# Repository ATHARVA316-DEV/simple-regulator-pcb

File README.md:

# SIMPLE REGULATOR PCB 🔌

## Project Overview
SIMPLE REGULATOR is a compact 2-layer linear voltage regulator PCB designed for beginner and academic use.  
This project demonstrates basic voltage regulation, PCB layout practices, and component placement using minimal components.

---

## Key Features
- Simple linear voltage regulator design  
- 2-layer PCB  
- Compact and minimal footprint  
- Input and output status LEDs  
- Beginner-friendly educational project  

---

## Components Used
| Reference | Component |
|---------|----------|
| U1 | Linear Voltage Regulator IC |
| R1, R2 | Resistors |
| C1, C2, C3 | Decoupling and filter capacitors |
| D1, D2 | LED indicators |
| J1 | Input connector |
| J2 | Output connector |

---

## Working Principle
1. DC input is supplied through connector J1  
2. Input LED (D1) indicates power availability  
3. The regulator IC (U1) stabilizes the input voltage  
4. Capacitors filter noise and improve voltage stability  
5. Regulated output is available at connector J2  
6. Output LED (D2) confirms regulated voltage  

---

## PCB Specifications
- Board Size: 46.45 mm × 15.44 mm  
- Layers: 2  
- Drill Size: 1.0 mm (4 holes)  
- Copper Pour: Ground plane  
- Design Tool: KiCad  

---

## Project Images
## Custom Etched PCB

Below is the manually fabricated PCB for the Simple Regulator project.  
The board was created using the **chemical etching method on an FR4 copper board**.

### Circuit Schematic

### PCB Routing

### 3D PCB View

### PCB Layout

### Drill Map

---

## How to Use
1. Provide DC input voltage at J1  
2. Ensure input voltage is within regulator specifications  
3. Check input LED for power indication  
4. Use regulated output from J2  

---

## Learning Outcomes
- Understanding linear voltage regulation  
- Basic PCB routing techniques  
- Decoupling capacitor placement  
- Ground plane implementation  

---

## License
This project is licensed under the MIT License.

---

## Author
Designed by Atharva M  
---

## Acknowledgment
This project was developed for academic and learning purposes.

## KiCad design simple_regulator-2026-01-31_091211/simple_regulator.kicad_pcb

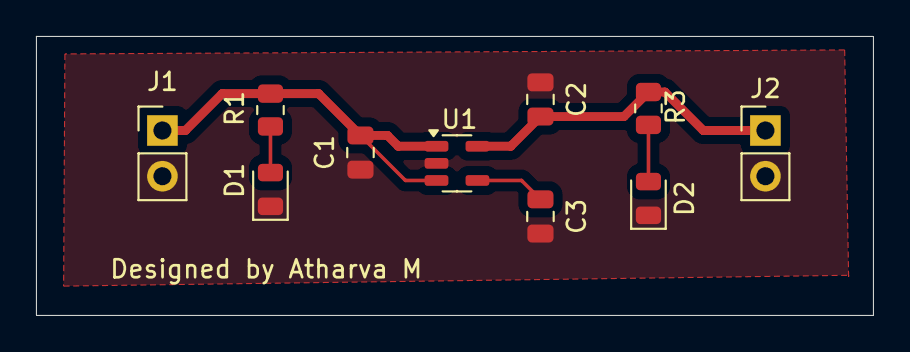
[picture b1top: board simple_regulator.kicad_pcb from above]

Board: 2 copper layers, 46.5 x 15.5 mm, 10 parts (0 on the bottom side), 6 nets.

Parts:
C1: 0.1uF; C_0805_2012Metric
C2: 2.2uF; C_0805_2012Metric
C3: 0.01uF; C_0805_2012Metric
D1: LED-RED; LED_0805_2012Metric
D2: LED-GREEN; LED_0805_2012Metric
J1, J2: Conn_01x02; PinHeader_1x02_P2.54mm_Vertical
R1: 649; R_0805_2012Metric
R3: 280; R_0805_2012Metric
U1: TPS79333-EP; SOT-23-5

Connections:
GND: C1.2, C2.2, C3.2, D1.1 (K), D2.1 (K), J1.2, J2.2, U1.2 (GND)
unnamed: D1.2 (A), R1.2
unnamed: D2.2 (A), R3.2
unnamed: C1.1, J1.1, R1.1, U1.1 (IN), U1.3 (EN)
unnamed: C2.1, J2.1, R3.1, U1.5 (OUT)
unnamed: C3.1, U1.4 (BP)

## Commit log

2026-02-03 Initial commit: Simple regulator PCB project
2026-02-03 Revise README for SIMPLE REGULATOR PCB project
    Updated the README to provide a comprehensive overview of the SIMPLE REGULATOR PCB project, including key features, components used, working principles, specifications, images, usage instructions, le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
2026-03-06 Add custom etched PCB section to README
    Added section for custom etched PCB with image.
